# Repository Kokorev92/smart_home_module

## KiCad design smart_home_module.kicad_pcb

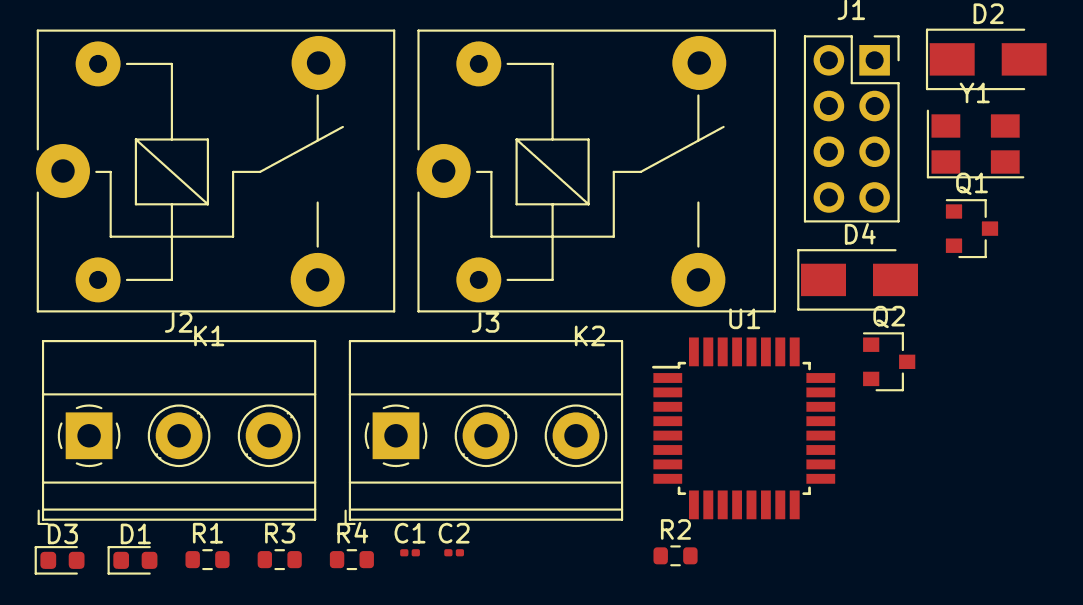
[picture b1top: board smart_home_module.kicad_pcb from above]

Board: 2 copper layers, 19 parts (0 on the bottom side), 14 nets, no tracks yet.

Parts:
C1, C2: 22p; C_0201_0603Metric
D1, D3: LED; LED_0603_1608Metric
D2, D4: D; D_SMA
J1: Conn_02x04_Odd_Even; PinSocket_2x04_P2.54mm_Vertical
J2, J3: Conn_01x03; TerminalBlock_Phoenix_MKDS-1,5-3_1x03_P5.00mm_Horizontal
K1, K2: DIPxx-1Cxx-51x; Relay_SPDT_SANYOU_SRD_Series_Form_C
Q1, Q2: BC817; SOT-23
R1, R4: 1k; R_0603_1608Metric
R2, R3: 220; R_0603_1608Metric
U1: ATmega328P-AU; TQFP-32_7x7mm_P0.8mm
Y1: 16Mhz; Crystal_SMD_5032-4Pin_5.0x3.2mm

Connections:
GND: C1.2, C2.2, Q1.2, Q2.2
unnamed: D1.1, D2.2, K1.2, Q1.3
unnamed: D1.2, R2.1
unnamed: D3.1, D4.2, K2.2, Q2.3
unnamed: D3.2, R3.1
unnamed: Q1.1, R1.1
unnamed: Q2.1, R4.1
unnamed: U1.4, U1.6
unnamed: U1.3, U1.5, U1.21
RELAY_1_NC: J2.3, K1.1
RELAY_2_NC: J3.3, K2.1
VIN: D2.1, D4.1, R2.2, R3.2
XTAL1: C1.1, U1.7, Y1.1
XTAL2: C2.1, U1.8, Y1.2

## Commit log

2021-05-26 git init
2021-05-26 wip: начал обвзяку
2021-05-26 wip: добавил два реле с обвязкой
2021-05-27 wip: добавил осцилятор и схему преобразователя напряжения на 3.3В
2021-05-27 wip: изменил схему резонатора, убрал преобразователь на 5В, чтобы добавить другой
